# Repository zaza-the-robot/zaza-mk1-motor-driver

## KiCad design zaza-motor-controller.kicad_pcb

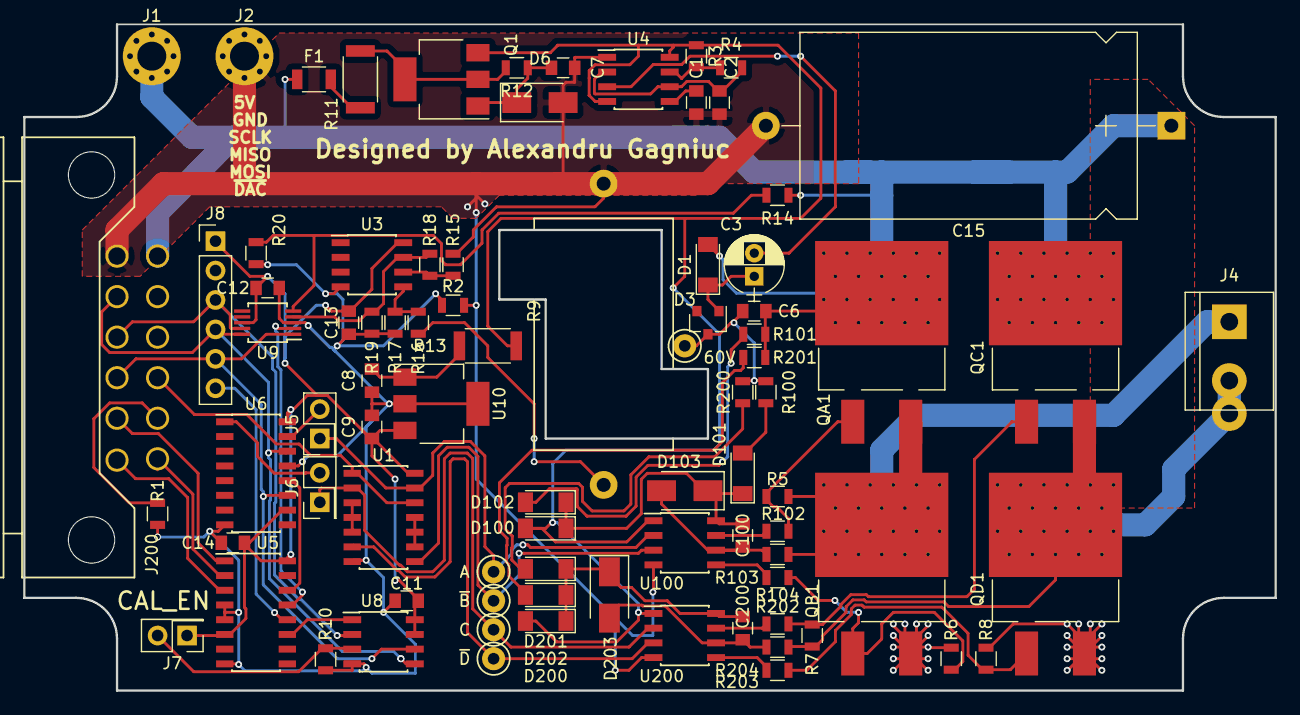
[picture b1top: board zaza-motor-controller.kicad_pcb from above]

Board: 2 copper layers, 108.0 x 57.5 mm, 84 parts (0 on the bottom side), 59 nets.

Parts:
C1: 1n; C_0805
C2: 100p; C_0805
C3: 1uF 100V; CP_Radial_D5.0mm_P2.00mm
C6, C7, C8, C9, C11, C12, C13, C14: 1uF; C_0805
C15: 100u 100V; CP_Axial_L29.0mm_D16.0mm_P35.00mm_Horizontal
C100, C200: 220n; C_0805
D1: 1N5711; D_MiniMELF_Standard
D3: BAR43; SOT-23
D6, D103, D203: 15.6V; D_SMA_Standard
D100, D101, D102, D200, D201, D202: 1N...; D_MiniMELF_Standard
F1: 100mA; R_1206
J1, J2: VIN; MountingHole_2.5mm_Pad_Via
J4: CONN_02X01; bornier2
J5: U; Pin_Header_Straight_2x01_Pitch2.54mm
J6: V; Pin_Header_Straight_2x01_Pitch2.54mm
J7: CAL_EN; Pin_Header_Straight_2x01_Pitch2.54mm
J8: CONN_01X06; Pin_Header_Straight_1x06_Pitch2.54mm
J200: MX120G; Molex_MX120G_02x06_3.5mm_36783-1201
Q1: NZT605; SOT-223-3Lead_TabPin2
QA1: DMN10; SOT-404-thermal-vias
QB1: DMN10; SOT-404-thermal-vias
QC1: DMN10; SOT-404-thermal-vias
QD1: DMN10; SOT-404-thermal-vias
R1, R2, R103, R203: 0R; R_0805
R3, R10, R12, R20, R100, R101, R200, R201: 10k; R_0805
R4: 47k; R_0805
R5, R6, R7, R8: 1M; R_0805
R9: 10 mOhm; R_Axial_Power_L25.0mm_W6.4mm_P27.94mm
R11, R13: 50R; R_2010
R14: 180k; R_0805
R15, R16, R19: 3.3k; R_0805
R17, R18: 100k; R_0805
R102, R104, R202, R204: 1k; R_0805
TP1: 60V; Test_Point_Keystone_5000-5004_Miniature
TP4: A; Test_Point_Keystone_5000-5004_Miniature
TP5: ~B; Test_Point_Keystone_5000-5004_Miniature
TP6: ~D; Test_Point_Keystone_5000-5004_Miniature
TP7: C; Test_Point_Keystone_5000-5004_Miniature
U1: 74HC00; SOIC-14_3.9x8.7mm_Pitch1.27mm
U3: LM358; SOIC-8_3.9x4.9mm_Pitch1.27mm
U4: LM555; SOIC-8_3.9x4.9mm_Pitch1.27mm
U5: 74HC138; SOIC-16_3.9x9.9mm_Pitch1.27mm
U6: 74HC595; SOIC-16_3.9x9.9mm_Pitch1.27mm
U8: AT25; SOIC-8_3.9x4.9mm_Pitch1.27mm
U9: ADS1018; MSOP-10_3x3mm_Pitch0.5mm
U10: LM7805; SOT-223-3Lead_TabPin2
U100, U200: IRS2003; SOIC-8_3.9x4.9mm_Pitch1.27mm

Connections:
+5V: C9.1, C11.2, C12.2, C13.2, C14.2, J7.1, J8.1, U1.14, U3.8, U5.6, U5.16, U6.10, U6.16, U8.7, U8.8, U9.8, U10.3
+15V: D100.2, D200.2, Q1.3, R3.1, R13.1, U4.4, U4.8, U100.1, U200.1
+48V: C6.2, C15.1, D1.2, F1.2, J1.1, J200.1, QA1.2, QC1.2, R14.2, R101.2, R201.2
/A: J5.1, TP4.1, U1.13, U100.2
/C: J6.1, TP7.1, U1.2, U200.2
/CS_ADDR0: J200.11, U5.1
/CS_ADDR1: J200.6, U5.2
/CS_ADDR2: J200.12, U5.3
/I_SENSE: R18.2, R19.1, U3.7, U9.4
/M+: J4.1, QA1.3, QB1.2, R5.2, R103.1
/M-: J4.2, QC1.3, QD1.2, R7.2, R203.1
/MISO: J8.3, J200.9, U8.2, U9.9
/MOSI: J8.4, J200.8, U6.14, U8.5, U9.10
/PUMP_OSC: C3.2, U4.3
/PWM: J200.4, U1.1, U1.12
/SCLK: J8.5, J200.10, U6.11, U8.6, U9.1
/V_SENSE: R14.1, R20.2, U9.5
/~B: TP5.1, U1.8, U100.3
/~CS_ADC: U5.13, U9.2
/~CS_DAC: J8.6, U5.12
/~CS_GPO: U5.14, U6.12
/~CS_ROM: U5.11, U8.1
/~D: TP6.1, U1.6, U200.3
GND: C8.2, C9.2, C11.1, C12.1, C13.1, C14.1, J8.2, R1.2, R2.1, R10.2, R17.2, R19.2, R20.1, U1.7, U3.4, U5.4, U5.5, U5.8, U6.8, U6.13, U8.4, U9.3, U10.2
GNDPWR: C1.2, C2.2, C7.2, C15.2, D6.2, J2.1, J200.7, R2.2, R9.2, R15.1, U4.1, U100.4, U200.4
GNDREF: J200.5, R1.1
HT: C6.1, D3.3, R100.2, R200.2, TP1.1
unnamed: C1.1, U4.5
unnamed: C2.1, R4.2, U4.2, U4.6
unnamed: C3.1, D1.1, D3.1
unnamed: C7.1, D6.1, Q1.1, R12.1
unnamed: C8.1, R13.2, U10.1
unnamed: C100.1, D100.1, D101.1, D102.1, D103.1, U100.8
unnamed: C100.2, D103.2, R103.2, U100.6
unnamed: C200.1, D200.1, D201.1, D202.1, D203.1, U200.8
unnamed: C200.2, D203.2, R203.2, U200.6
unnamed: D101.2, R100.1
unnamed: D102.2, R101.1
unnamed: D201.2, R200.1
unnamed: D202.2, R201.1
unnamed: F1.1, R11.1
unnamed: J5.2, U6.15
unnamed: J6.2, U6.1
unnamed: J7.2, R10.1, U8.3
unnamed: Q1.2, R11.2, R12.2
unnamed: QA1.1, R5.1, R102.2
unnamed: QB1.1, R6.1, R104.2
unnamed: QB1.3, QD1.3, R6.2, R8.2, R9.1, R16.1
unnamed: QC1.1, R7.1, R202.2
unnamed: QD1.1, R8.1, R204.2
unnamed: R3.2, R4.1, U4.7
unnamed: R15.2, R18.1, U3.6
unnamed: R16.2, R17.1, U3.5
unnamed: R102.1, U100.7
unnamed: R104.1, U100.5
unnamed: R202.1, U200.7
unnamed: R204.1, U200.5
unnamed: U1.3, U1.4, U1.5
unnamed: U1.9, U1.10, U1.11

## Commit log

2017-10-21 Add (non-working) rev0 of design
2017-10-21 Rev1 dev
2017-10-24 schematic: Getting closer to rev 1
    Replace dscrete FET driver with IRS2003.
    Add ADC, and other cool shit.
2017-10-26 Incrase schematic chooch factor by warp 9
2017-10-26 Layout choochiness over nine thousand
2017-10-27 schematic moar cool scheise
2017-10-27 moar layout
2017-10-28 fix the darn author's name
2017-11-05 Add Rev 1 schematic
    We've changed the FET driving circuit to use IRS2003 drivers instead
    of discrete logic. There is also an ADC and a SPI bus with encoded
    chip-select.
2017-11-05 Add layout for Revision 1
    Now made to fit in an off-the-shelf plastic box.
2017-11-12 Organize F. Fab layer to emphasize compnent values
    The F. Fab layer is useful for manual assembly. In this case, it's
    very useful to emphasize the component values.
2017-11-12 Fix fill in copper pours
